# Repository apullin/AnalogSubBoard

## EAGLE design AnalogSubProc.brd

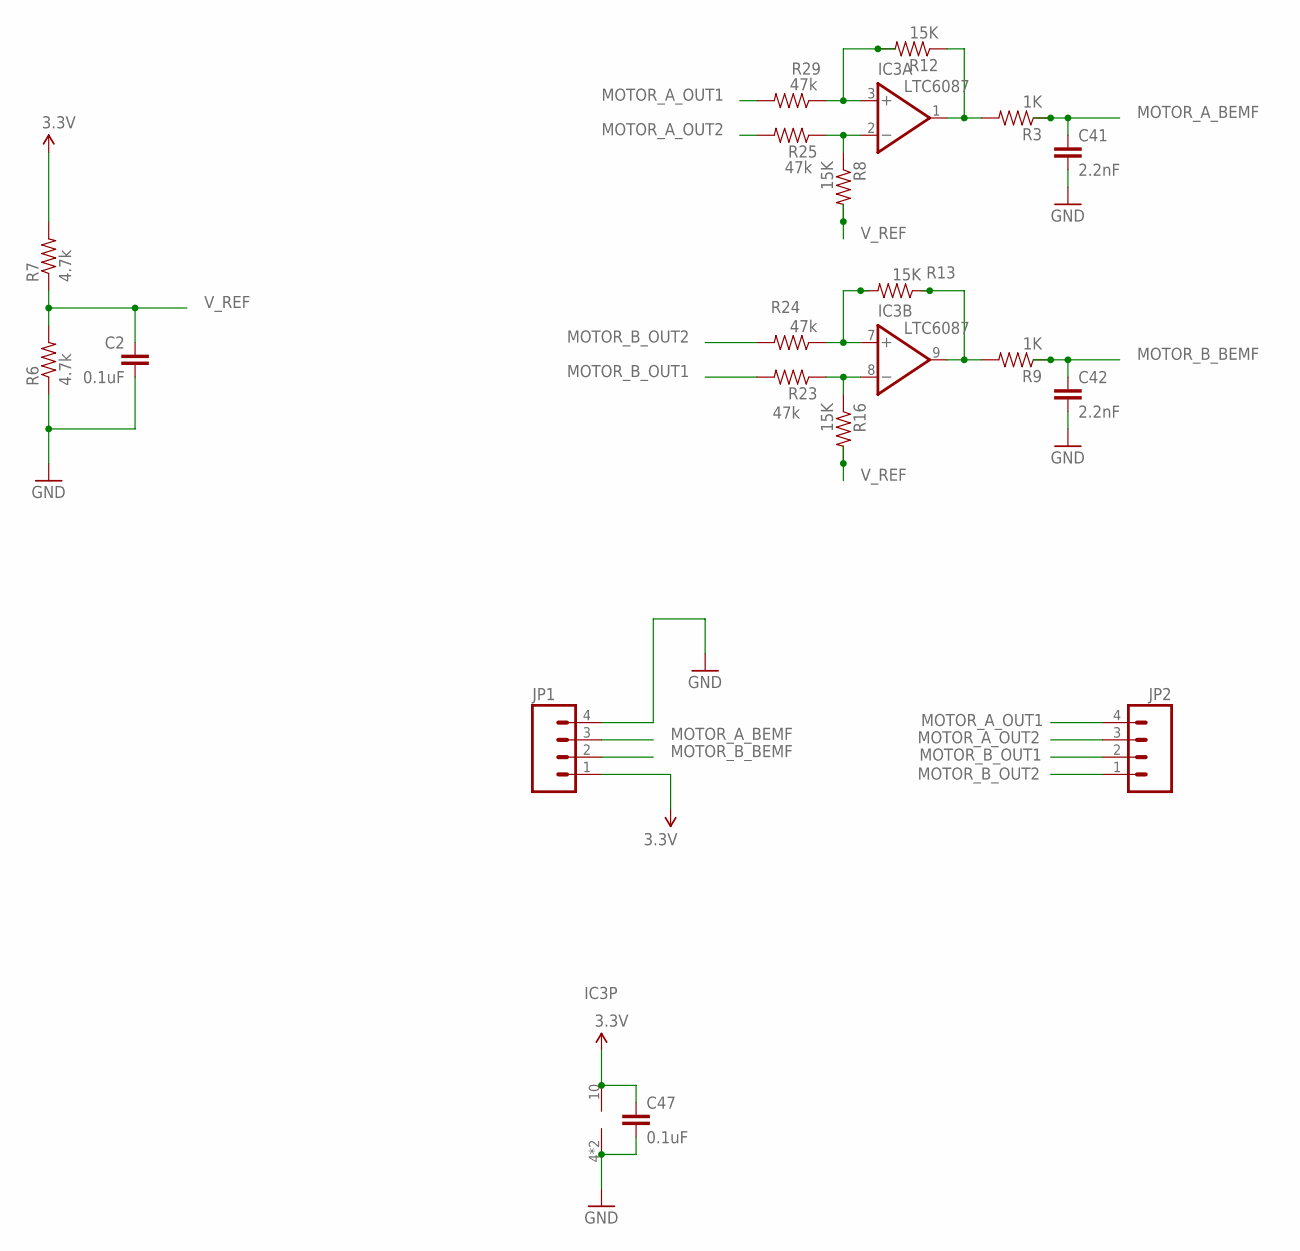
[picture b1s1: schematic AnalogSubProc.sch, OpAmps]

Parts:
C2, C47: 0.1uF; 0402-CAP
C41, C42: 2.2nF; 0402-CAP
IC3: LTC6087; DFN-10
JP1, JP2: M041.27MM; 1X04-1.27MM
R3, R9: 1K; 0402-RES
R6, R7: 4.7k; 0402-RES
R8, R12, R13, R16: 15K; 0402-RES
R23, R24, R25, R29: 47k; 0402-RES

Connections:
3.3V: C47.1, IC3.10 (V+), JP1.1, R7.2
GND: C2.2, C41.2, C42.2, C47.2, IC3.4 (V-), IC3.PAD (V-), JP1.4, R6.1
MOTOR_A_BEMF: C41.1, JP1.3, R3.1
MOTOR_A_OUT1: JP2.4, R29.2
MOTOR_A_OUT2: JP2.3, R25.2
MOTOR_B_BEMF: C42.1, JP1.2, R9.1
MOTOR_B_OUT1: JP2.2, R23.2
MOTOR_B_OUT2: JP2.1, R24.2
unnamed: IC3.7 (+IN), R13.2, R24.1
unnamed: IC3.8 (-IN), R16.1, R23.1
unnamed: IC3.3 (+IN), R12.2, R29.1
unnamed: IC3.2 (-IN), R8.1, R25.1
unnamed: IC3.1 (OUT), R3.2, R12.1
unnamed: IC3.9 (OUT), R9.2, R13.1
V_REF: C2.1, R6.2, R7.1, R8.2, R16.2

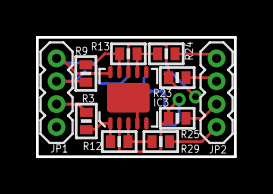
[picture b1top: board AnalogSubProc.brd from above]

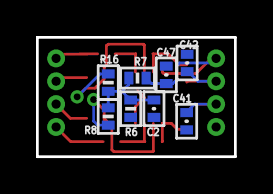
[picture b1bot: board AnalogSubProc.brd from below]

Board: 2 copper layers, 11.0 x 6.6 mm, 19 parts (8 on the bottom side), 15 nets.

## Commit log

2014-09-04 Initial commit of schematic and board.
2014-09-04 Adding .gitignore
2014-09-04 Smaller board succesfully routed.

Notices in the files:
parts and their libraries:
SparkFun-Connectors: Licensing: Creative Commons ShareAlike 4.0 International - https://creativecommons.org/licenses/by-sa/4.0
biomimetic: UC Regents. All rights reserved.
